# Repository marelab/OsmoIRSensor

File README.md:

OsmoIRSensor
IR Water &amp; Fluid detection Sensor based on ATTINY45. 
- KiCad Shematic & PCB included under hardware
- Firmware for ATTINY45 included under software

The Sensor was designed for Osmosi waterlevel control. 
It is designed to be full encapsulated in a EPOXY case. 
The hole design an maufacturing process as well as the 
technical backgrounds for the IR detection 
is described under
https://www.marelab.org

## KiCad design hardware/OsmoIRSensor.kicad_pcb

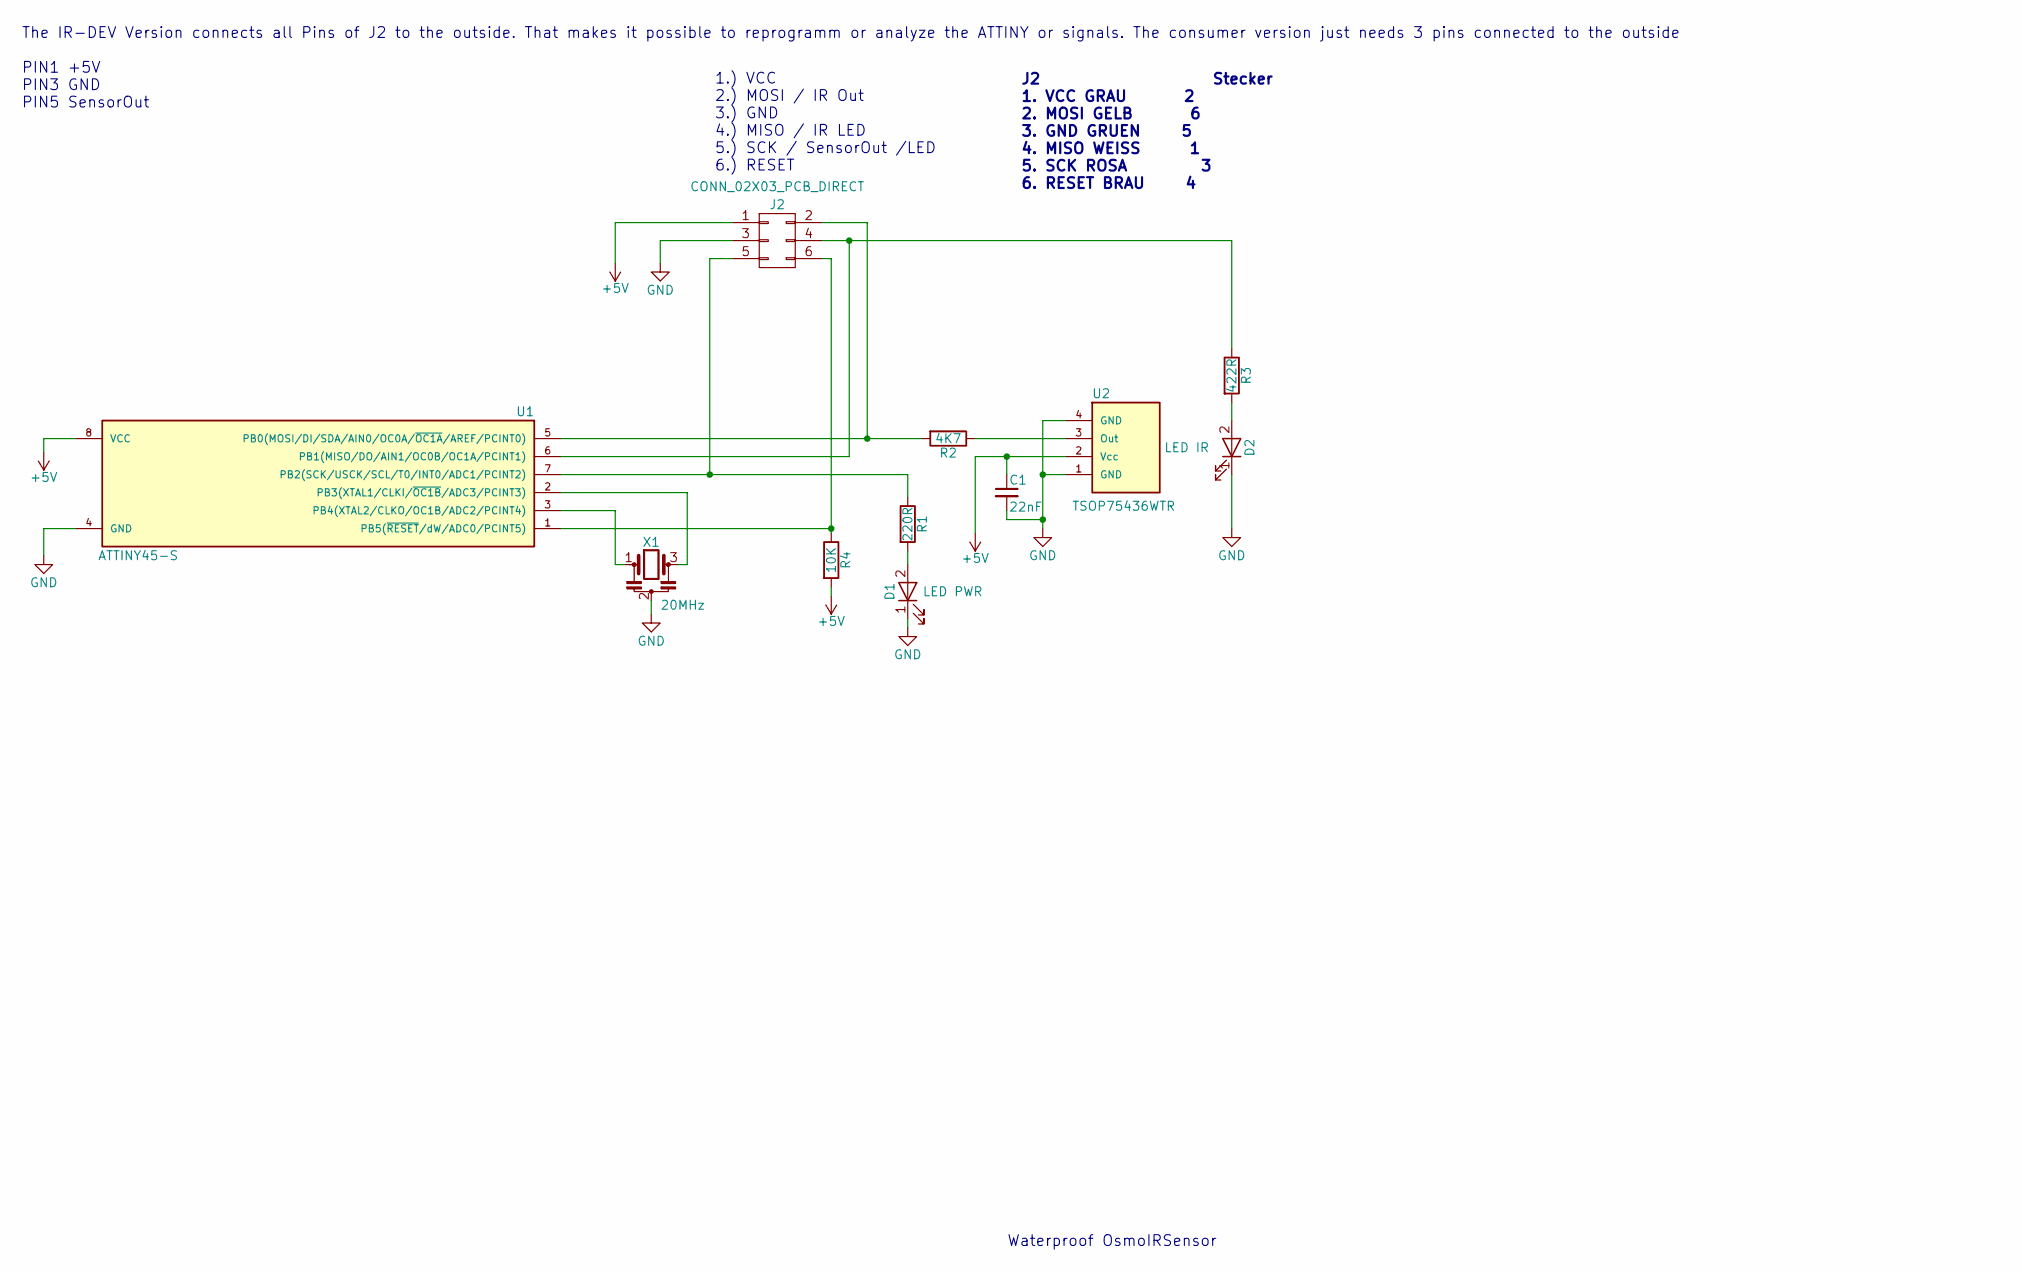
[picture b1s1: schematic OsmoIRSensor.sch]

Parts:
C1: 22nF; R_0805
D1: LED PWR; LED_0805
D2: LED IR; LED_PLCC-2
J2: CONN_02X03_PCB_DIRECT; CON3x2PCB
R1: 220R; R_0805
R2: 4K7; R_0805
R3: 422R; R_0805
R4: 10K; R_0805
U1: ATTINY45-S; SOIC-8
U2: TSOP75436WTR; SMD-IR
X1: 20MHz; RESONATOR

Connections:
+5V: C1.1, J2.1, R4.2, U1.8 (VCC), U2.2 (Vcc)
GND: C1.2, D1.1 (K), D2.1 (K), J2.3, U1.4 (GND), U2.1 (GND), U2.4 (GND), X1.2
unnamed: D1.2 (A), R1.2
unnamed: D2.2 (A), R3.2
unnamed: J2.2, R2.2, U1.5 (PB0(MOSI/DI/SDA/AIN0/OC0A/~OC1A~/AREF/P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)
unnamed: J2.4, R3.1, U1.6 (PB1(MISO/DO/AIN1/OC0B/OC1A/PCINT1))
unnamed: J2.5, R1.1, U1.7 (PB2(SCK/USCK/SCL/T0/INT0/ADC1/PCINT2))
unnamed: J2.6, R4.1, U1.1 (PB5(~RESET~/dW/ADC0/PCINT5))
unnamed: R2.1, U2.3 (Out)
unnamed: U1.2 (PB3(XTAL1/CLKI/~OC1B~/ADC3/PCINT3)), X1.3
unnamed: U1.3 (PB4(XTAL2/CLKO/OC1B/ADC2/PCINT4)), X1.1

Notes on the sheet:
Waterproof OsmoIRSensor
1.) VCC 2.) MOSI / IR Out 3.) GND 4.) MISO / IR LED 5.) SCK / SensorOut /LED 6.) RESET
The IR-DEV Version connects all Pins of J2 to the outside. That makes it possible to reprogramm or analyze the ATTINY or signals. The consumer version just needs 3 pins connected to the outside PIN1 +5V PIN3 GND PIN5 SensorOut
J2 Stecker 1. VCC GRAU 2 2. MOSI GELB 6 3. GND GRUEN 5 4. MISO WEISS 1 5. SCK ROSA 3 6. RESET BRAU 4

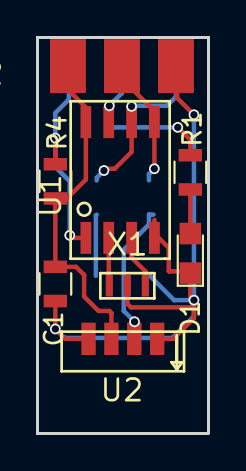
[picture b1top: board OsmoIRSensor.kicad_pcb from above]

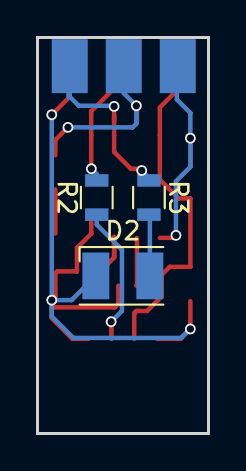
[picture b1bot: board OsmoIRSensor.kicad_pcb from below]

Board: 2 copper layers, 9.5 x 22.0 mm, 11 parts (3 on the bottom side), 11 nets.

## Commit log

2017-03-14 :lollipop: Added .gitattributes & .gitignore files
2017-03-14 Marelab IR Water Sensor Initial Version
2017-03-14 Added GPL2 licens
2017-03-17 - Corrected IC Pads Size - Gerber Files added for 10x9,1cm panelized pcb - 3D Printer Files for optical Barrier added - Pin Desc. for DEV Cabel
2017-03-28 - Sensor Interrupt Handling changed - 20MHz Fuse Setting no CHKDIV/8
